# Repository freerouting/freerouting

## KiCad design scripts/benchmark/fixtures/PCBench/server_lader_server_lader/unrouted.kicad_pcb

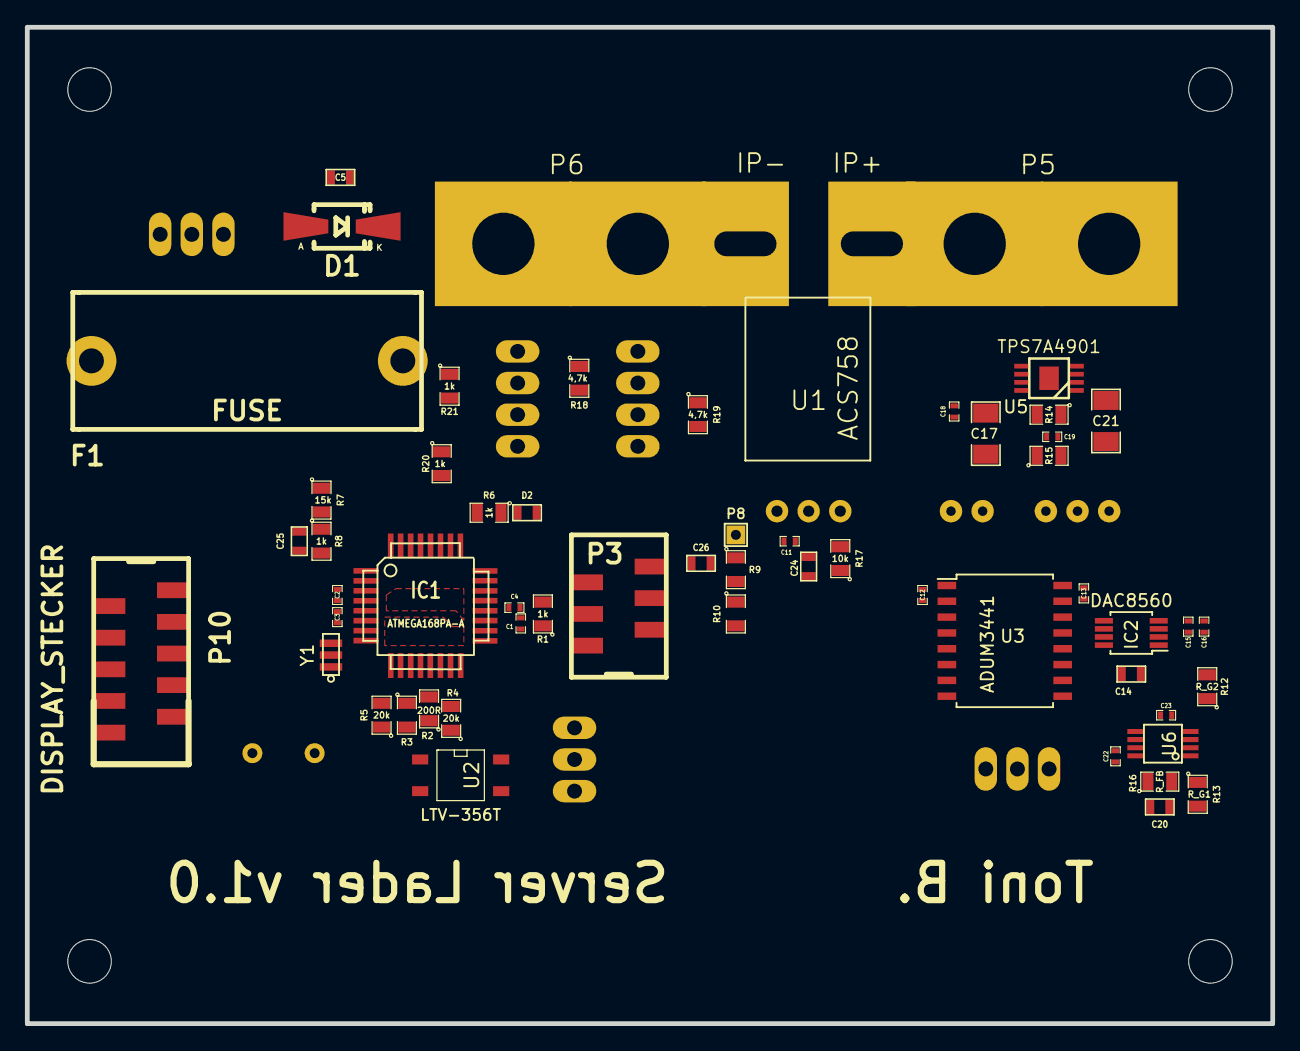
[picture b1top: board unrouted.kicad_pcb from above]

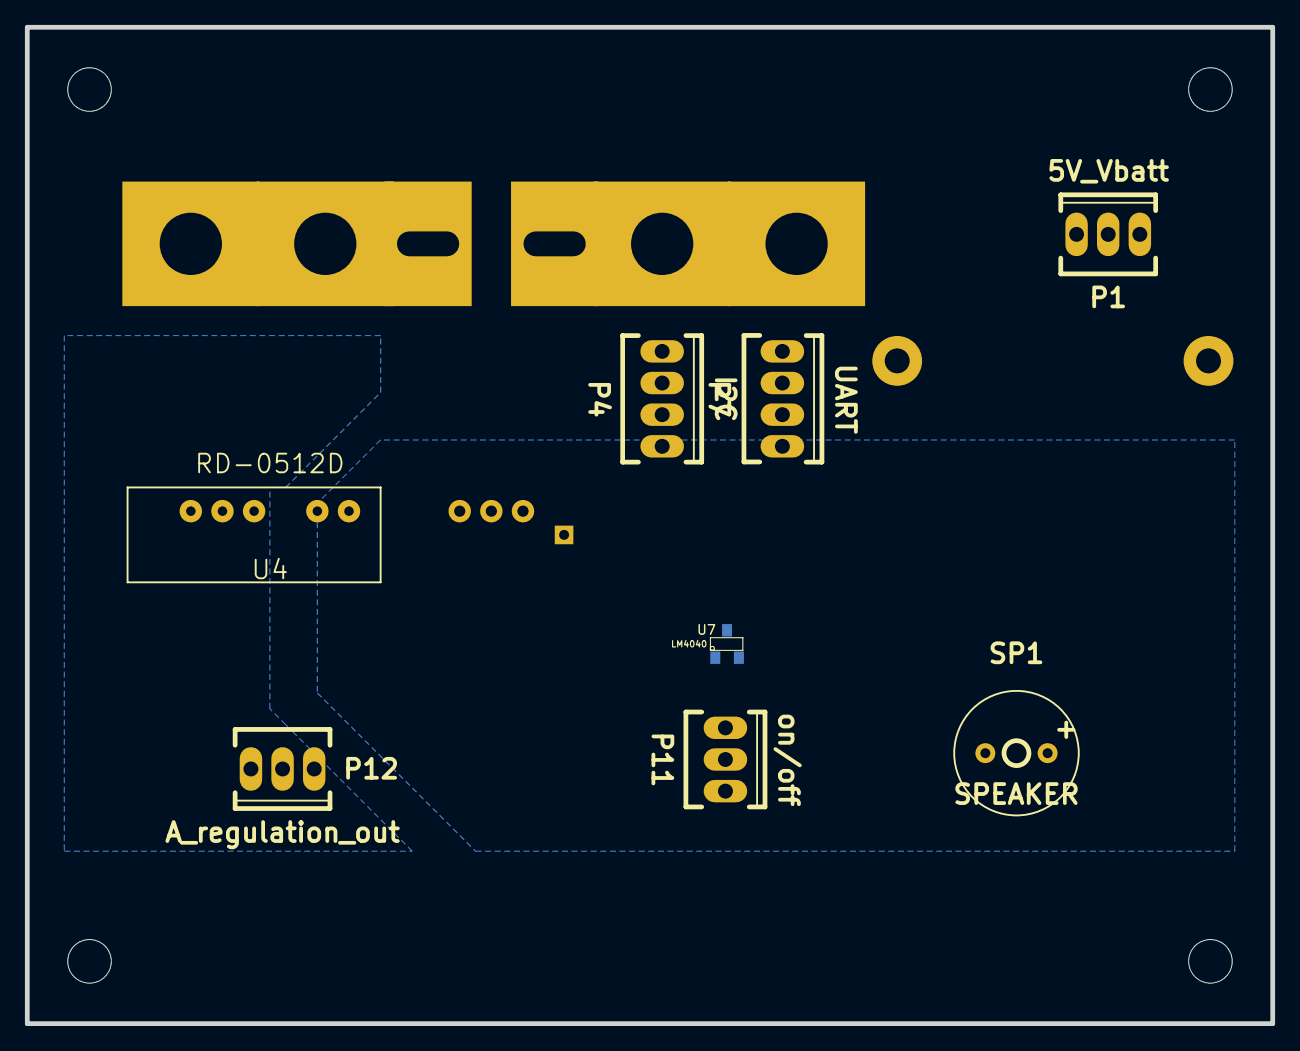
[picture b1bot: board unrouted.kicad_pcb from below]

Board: 2 copper layers, 100.0 x 80.0 mm, 66 parts (8 on the bottom side), 51 nets, no tracks yet.

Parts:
C1, C2, C3, C4, C11, C12, C13, C15, C16, C22, C23: 100nF; SMD-0402
C5, C14, C24: 1uF; SMD-0603
C17, C21: 10uF; SMD-1206
C18, C19: 10nF; SMD-0402
C20: C_comp; SMD-0603
C25: 100nF; SMD-0603
C26: C; SMD-0603
D1: ZENER 5,6V; Diode-Universal-SMA-SMB_Handsoldering
D2: LED; SMD-0603
F1: FUSE; fuse_holder_Schurther
IC1: ATMEGA168PA-A; TQFP-32
IC2: DAC8560; MSOP-8_3x3mm_Pitch0.65mm
Outl: EuroBoard_halb_Type-I_100mmX80mm_holes
P1: 5V_Vbatt; Socket_MOLEX-KK-RM2-54mm_Lock_3pin_straight
P3: CONN_02X03; micro_match3x2
P4: I2C; Socket_MOLEX-KK-RM2-54mm_Lock_4pin_straight
P5: IP+; power_terminal
P6: IP-; power_terminal
P7: UART; Socket_MOLEX-KK-RM2-54mm_Lock_4pin_straight
P8: CONN_01X01; SIL-1
P10: DISPLAY_STECKER; micro_match5x2
P11: on/off; Socket_MOLEX-KK-RM2-54mm_Lock_3pin_straight
P12: A_regulation_out; Socket_MOLEX-KK-RM2-54mm_Lock_3pin_straight
R1, R6, R8, R20, R21: 1k; SMD-0805
R2: 200R; SMD-0805
R3, R9, R10: R; SMD-0805
R4, R5: 20k; SMD-0805
R7: 15k; SMD-0805
R12: R_G2; SMD-0805
R13: R_G1; SMD-0805
R14: 33k; SMD-0805
R15, R17: 10k; SMD-0805
R16: R_FB; SMD-0805
R18, R19: 4,7k; SMD-0805
SP1: SPEAKER; Buzzer_AI-1027-TWT-5V-R
U1: ACS758; ACS758_PFF
U2: LTV-356T; SO-4
U3: ADUM3441; SOIC-16_7.5x10.3mm_Pitch1.27mm
U4: RD-0512D; RD-xx12D
U5: TPS7A4901; MSOP-8_power_pad
U6: OPA827; SSOP-8
U7: LM4040; SOT-23
Y1: RESONATEUR; CerOsc_3,2x1,3

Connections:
+5VA: C13.1, C14.1, C19.1, C21.1, IC2.1, R14.1, U3.10, U3.16, U5.1
+12V: C17.1, C22.1, U4.6, U5.5, U5.8, U6.7
-12V: C23.2, U4.4, U6.4
/A: IC1.32, P10.2
/B: IC1.1, P10.3
/CSB: IC1.10, P10.10, R5.2
/MISO: IC1.16, P3.1, P10.7
/MOSI: IC1.15, P3.4, P10.6, U3.5
/RS: IC1.9, P10.9
/RST: IC1.29, P3.5
/S: IC1.2, P10.4
/SCK: IC1.17, P3.3, P10.8, U3.4
/SCL: IC1.28, P4.3, R18.2
/SDA: IC1.27, P4.2, R19.2
/SS_DAC: IC1.14, R4.2, U3.3
/U_Netzteil: C25.1, IC1.23, R7.2, R8.1
/U_Strom: C24.1, IC1.25, R17.1
/U_reserve: C26.1, IC1.24, R9.2, R10.1
/V_current: C20.1, P12.2, R16.1, U6.6
/Vref: C15.1, C16.1, IC2.2, R12.2
/on: R2.1, U2.1
AGND: C13.2, C14.2, C15.2, C16.2, C17.2, C18.2, C21.2, C22.2, C23.1, IC2.8, P12.1, R13.1, R15.2, U3.9, U3.15, U4.5, U5.4, U5.9
GND: C1.2, C2.2, C3.2, C4.2, C5.2, C11.2, C12.2, C24.2, C25.2, C26.2, D1.1, D2.2, IC1.3, IC1.5, IC1.19, IC1.21, P1.1, P3.6, P4.1, P7.1, P10.5, R8.2, R10.2, SP1.2, U1.2, U2.2, U3.2, U3.8, U4.2, U7.2, Y1.2
unnamed: C4.1, IC1.20, R1.2, U7.1
unnamed: C18.1, U5.6
unnamed: C19.2, R14.2, R15.1, U5.2
unnamed: C20.2, R12.1, R13.2, R16.2, U6.2
unnamed: D2.1, R6.1
unnamed: F1.1, P1.2
unnamed: IC1.7, Y1.3
unnamed: IC1.8, Y1.1
unnamed: IC1.11, R3.1
unnamed: IC1.12, R2.2
unnamed: IC1.26, R6.2
unnamed: IC1.30, R20.2
unnamed: IC1.31, R21.2
unnamed: IC2.3, IC2.4, U6.3
unnamed: IC2.5, U3.14
unnamed: IC2.6, U3.13
unnamed: IC2.7, U3.12
unnamed: P1.3, R7.1
unnamed: P5.1, U1.4
unnamed: P6.1, U1.5
unnamed: P7.2, R20.1
unnamed: P7.3, R21.1
unnamed: P8.1, R9.1
unnamed: P11.1, U2.3
unnamed: P11.2, P11.3, U2.4
unnamed: R3.2, SP1.1
unnamed: R17.2, U1.3
VCC: C1.1, C2.1, C3.1, C5.1, C11.1, C12.1, D1.2, F1.2, IC1.4, IC1.6, IC1.18, P3.2, P4.4, P7.4, P10.1, R1.1, R4.1, R5.1, R18.1, R19.1, U1.1, U3.1, U3.7, U4.1

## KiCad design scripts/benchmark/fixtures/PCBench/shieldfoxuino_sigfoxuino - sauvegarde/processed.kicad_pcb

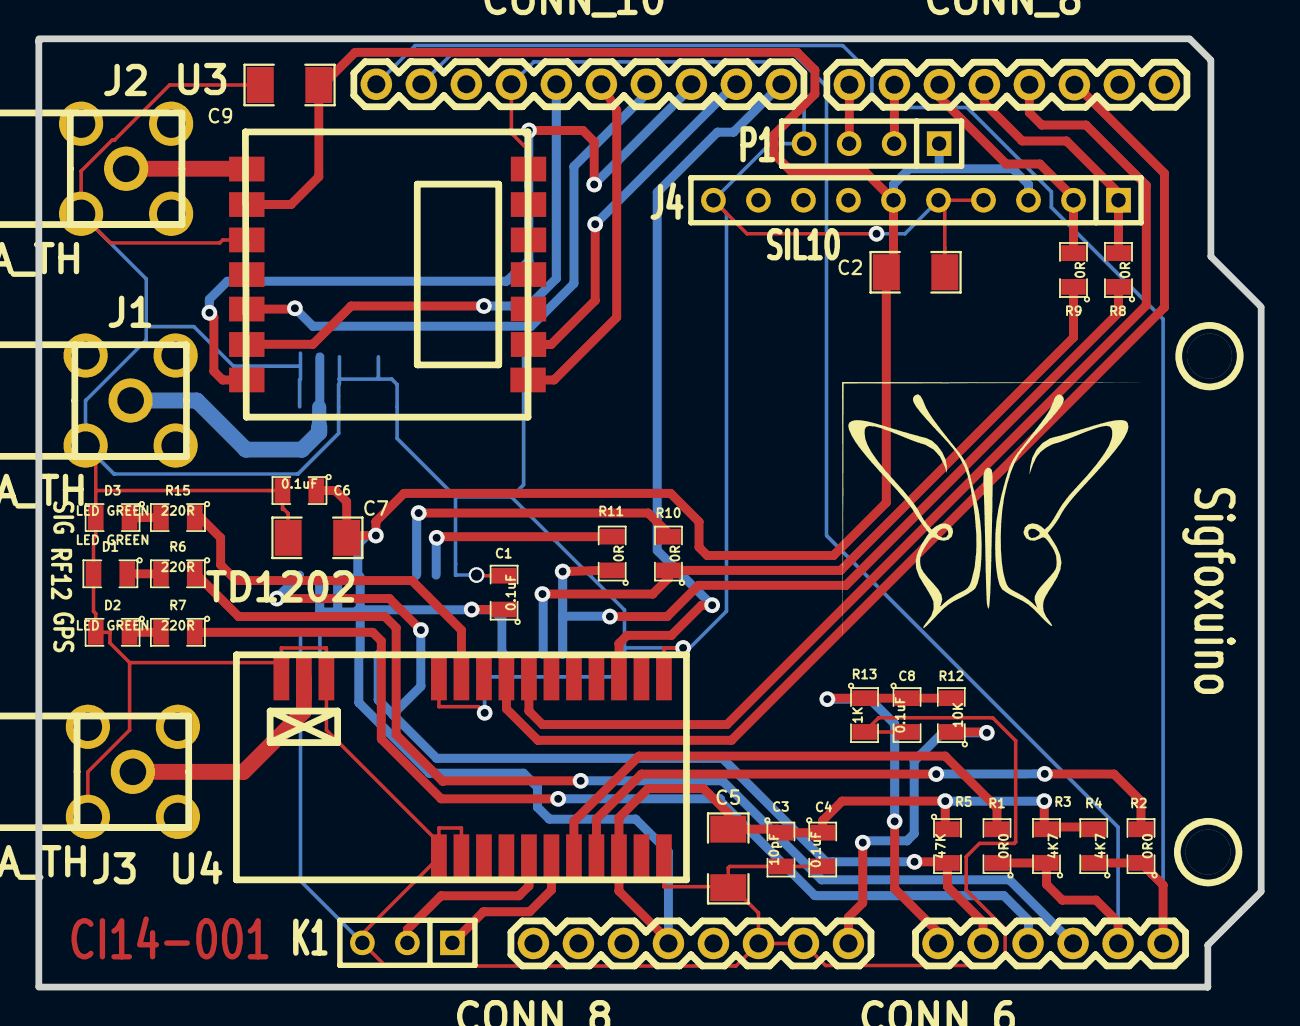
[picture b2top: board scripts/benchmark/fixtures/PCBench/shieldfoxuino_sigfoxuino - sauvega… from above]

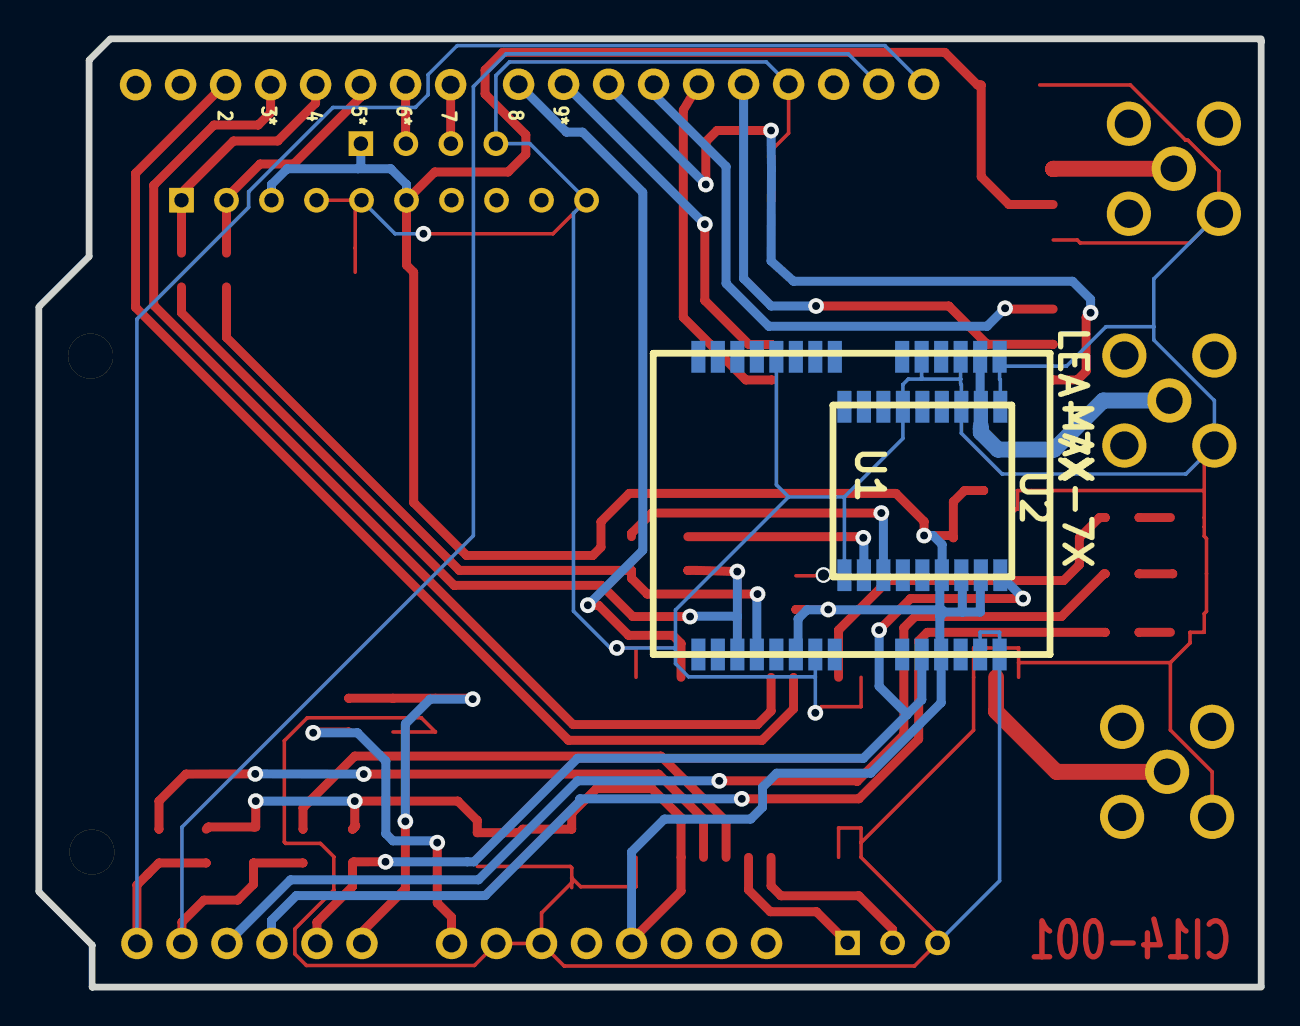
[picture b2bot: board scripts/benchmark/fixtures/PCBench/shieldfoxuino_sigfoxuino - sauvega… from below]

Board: 2 copper layers, 69.0 x 53.5 mm, 42 parts (2 on the bottom side), 36 nets.

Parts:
C1, C4, C6, C8: 0.1uF; SM0805
C2, C5, C7: 10uF/9V; SM1206
C3: 10pF; SM0805
C9: 1uF/9V; SM1206
CON6_1: CONN_6; Con6
CON8_1, CON8_2: CONN_8; Con8
CON10_1: CONN_10; Con10
D1, D2, D3: LED GREEN; SM0805
J1, J2, J3: SMA_TH; SMA-SMB_right_angle
J4: SIL10; SIL-10
K1: CONN_3; SIL-3
P1: CONN_4; SIL-4
R1, R2: 0R0; SM0805
R3, R4: 4K7; SM0805
R5: 47K; SM0805
R6, R7, R15: 220R; SM0805
R8, R9, R10, R11: 0R; SM0805
R12: 10K; SM0805
R13: 1K; SM0805
U1: LEA-7X; LEA-xx
U2: MAX-7X; MAX-xx
U3: RFM12
U4: TD1202
V4, V5: 1pin

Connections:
+3.3V: C1.1, C2.1, C3.1, C4.1, C5.1, C6.1, C7.1, C9.1, CON8_1.4, J4.3, J4.6, P1.1, R3.2, R4.2, R5.1, U1.6, U1.11, U2.6, U2.7, U2.8, U3.9, U4.9
/PB0: CON10_1.1, U4.14
/PB1: CON10_1.2, U3.2
/PB2: CON10_1.3, U3.14
/PB3: CON10_1.4, U3.12
/PB4: CON10_1.5, U3.1
/PB5: CON10_1.6, U3.13
/PC0: C8.1, CON6_1.1, R12.2, R13.1
/PC1: CON6_1.2, R5.2, U1.10, U2.9
/PC2: CON6_1.3, R7.1
/PC3: CON6_1.4, R6.1
/PD2: CON8_2.3, U4.19
/PD3: CON8_2.4, U4.18
/PD4: CON8_2.5, J4.1, R8.2
/PD5: CON8_2.6, J4.2, R9.2
/PD6: CON8_2.7, P1.2
/PD7: CON8_2.8, P1.3
/RF_GPS: J1.1, U1.16, U2.11
/RF_RF12: J2.1, U3.8
/RF_SIG: J3.1, U4.24
/RX_SFT: R8.1, R11.1, U1.3
/SCL: CON6_1.6, CON10_1.10, R2.1, R4.1
/SDA: CON6_1.5, CON10_1.9, R1.1, R3.1
/STATUS_SIG: R15.1, U4.21
/TX_SFT: R9.1, R10.1, U1.4
/VIN: CON8_1.8, R12.1
GND: C1.2, C2.2, C3.2, C4.2, C5.2, C6.2, C7.2, C8.2, C9.2, CON8_1.6, CON8_1.7, CON10_1.7, D1.2, D2.2, D3.2, J1.2, J2.2, J3.2, J4.4, J4.5, J4.10, K1.3, P1.4, R13.2, U1.7, U1.13, U1.14, U1.15, U1.17, U1.19, U1.24, U2.1, U2.10, U2.12, U2.15, U3.7, U3.10, U4.1, U4.2, U4.11, U4.12, U4.22, U4.23, U4.25
unnamed: R2.2, U4.8
unnamed: K1.2, U4.5
unnamed: K1.1, U4.6
unnamed: R11.2, U2.2
unnamed: R10.2, U2.3
unnamed: R1.2, U4.7
unnamed: D2.1, R7.2
unnamed: D1.1, R6.2
unnamed: D3.1, R15.2

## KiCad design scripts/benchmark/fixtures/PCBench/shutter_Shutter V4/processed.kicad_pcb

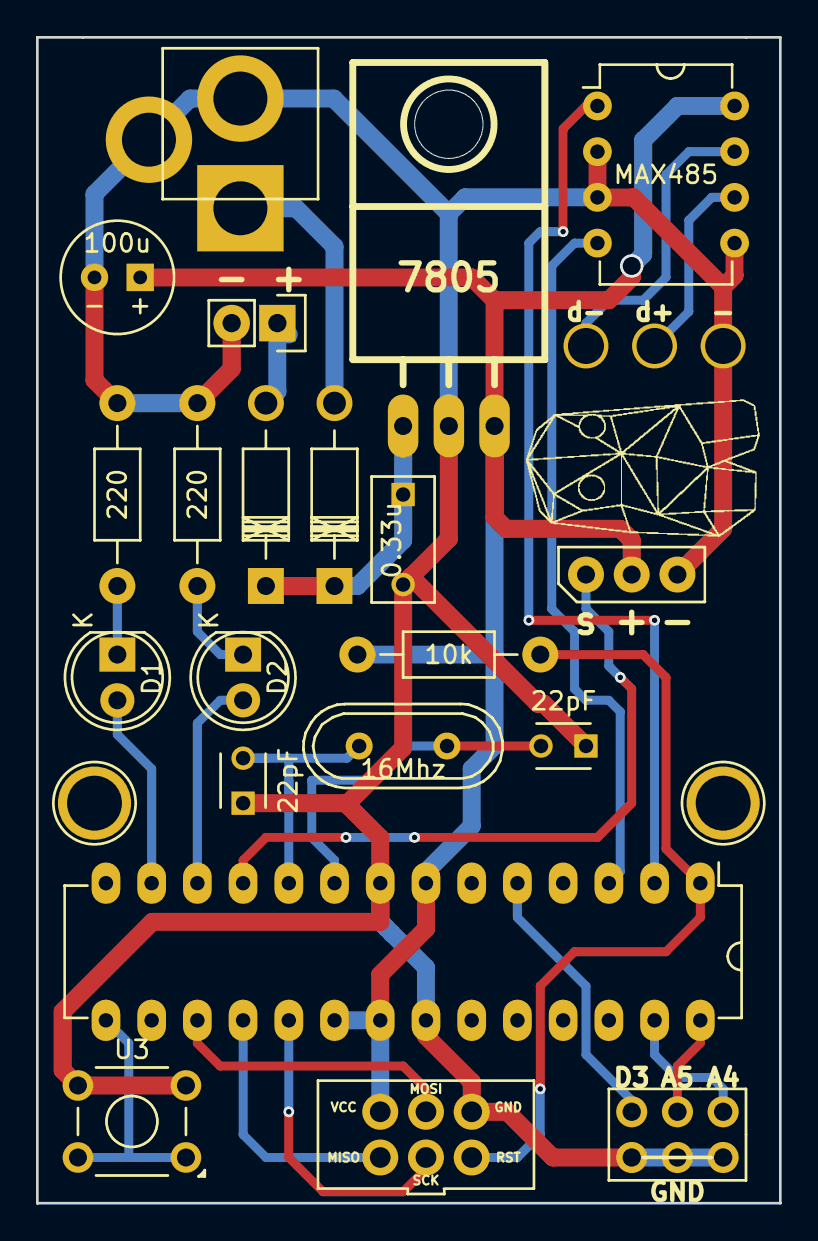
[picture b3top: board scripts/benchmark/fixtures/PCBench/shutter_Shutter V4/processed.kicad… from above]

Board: 2 copper layers, 41.3 x 64.8 mm, 23 parts (0 on the bottom side), 24 nets.

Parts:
C1, C2: 22pF; C_Disc_D3_P2.5
C3: 100u; CP_VERT_6.3
C4: 0.33u; C_Rect_L7_W3.5_P5
CON1: AVR-ISP-6; CONN_ISP_6
CON2: BARREL_JACK; JACK_ALIM
D1, D2: LED; LED-5MM
D3, D4: 1N4004; Diode_DO-41_SOD81_Horizontal_RM10
IC1: ATMEGA328-P; DIP-28_W7.62mm_LongPads
K1: XLR3; CONN_075_3
LOGO: LOGO
P1: CONN_SERVO
P2: CONN_01X02; Pin_Header_Straight_1x02
P3: CONN_02X03; Pin_Header_Straight_2x03
R1: 10k; Resistor_Horizontal_RM10mm
R2, R3: 220; Resistor_Horizontal_RM10mm
U1: MAX485; DIP-8_W7.62mm
U2: 7805; TO220_HORYZ
U3: DIP_SWITCH; SW_TH_Tactile_Omron_B3F-10xx
Y1: 16Mhz; Crystal_HC49-U_Vertical

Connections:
/A4: IC1.27, P3.1
/A5: IC1.28, P3.3
/D+: K1.3, U1.6
/D-: K1.2, U1.7
/DMX_LEARN: IC1.15, U3.1, U3.2
/DMX_RX: IC1.2, U1.1
/DMX_TX: IC1.3, U1.4
/MISO: CON1.1, IC1.18
/MOSI: CON1.4, IC1.17
/PWM_OUT_3: IC1.5, P3.5
/RST: CON1.5, IC1.1, R1.2
/SCK: CON1.3, IC1.19
/SERVO: IC1.11, P1.1
GND: C1.1, C2.1, C3.2, C4.2, CON1.6, CON2.2, CON2.3, IC1.8, IC1.22, K1.1, P1.3, P2.2, P3.2, P3.4, P3.6, R2.2, R3.2, U1.2, U1.3, U1.5, U2.2, U3.3, U3.4
unnamed: C1.2, IC1.9, Y1.1
unnamed: C2.2, IC1.10, Y1.2
unnamed: C4.1, D3.1, D4.1, U2.1
unnamed: CON2.1, D3.2
unnamed: D1.1, R2.1
unnamed: D1.2, IC1.13
unnamed: D2.1, R3.1
unnamed: D2.2, IC1.12
unnamed: D4.2, P2.1
VCC: C3.1, CON1.2, IC1.7, IC1.20, IC1.21, P1.2, R1.1, U1.8, U2.3
